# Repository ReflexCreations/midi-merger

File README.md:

# MIDI-merger

MIDI-merger is meant to be an n-to-1 merger of MIDI data. That is, you connect multiple MIDI sources with multiple cables, and all the messages sent through those are sent to a single port.

It is currently in development on the `develop` branch.

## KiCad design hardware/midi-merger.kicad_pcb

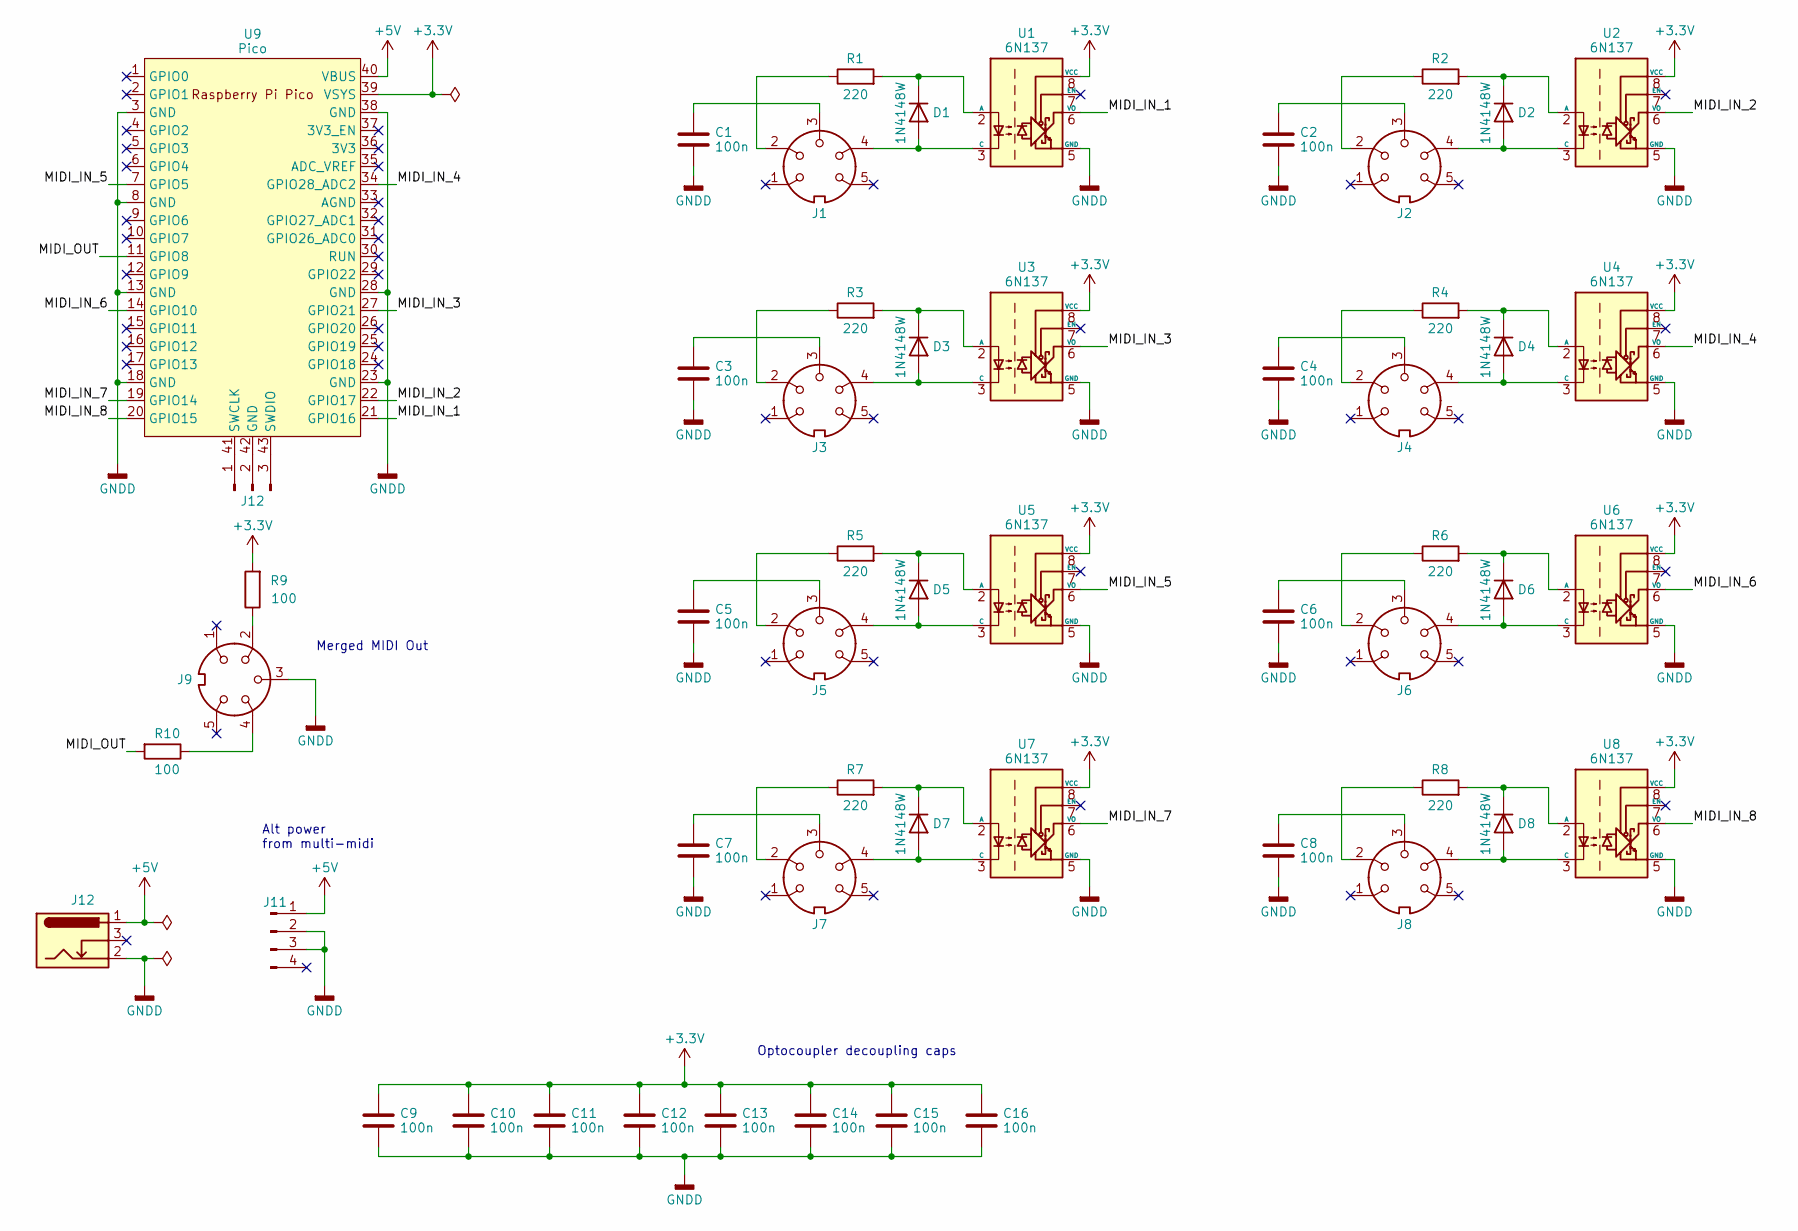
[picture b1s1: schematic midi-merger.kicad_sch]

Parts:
C1, C2, C3, C4, C5, C6, C7, C8, C9, C10, C11, C12, C13, C14, C15, C16: 100n; C_0603_1608Metric; LCSC C14663
D1, D2, D3, D4, D5, D6, D7, D8: 1N4148W; D_SOD-123; LCSC C81598
J1, J2, J3, J4, J5, J6, J7, J8, J9: DIN-5
J11: Conn_01x04_Pin; JST_EH_S4B-EH_1x04_P2.50mm_Horizontal
J12: Conn_01x03_Pin; JST_ACH_BM03B-ACHSS-GAN-ETF_1x03-1MP_P1.20mm_Vertical; LCSC C160389
R1, R2, R3, R4, R5, R6, R7, R8: 220; R_0603_1608Metric; LCSC C22962
R9, R10: 100; R_0603_1608Metric; LCSC C22775
U1, U2, U3, U4, U5, U6, U7, U8: 6N137; SSO-8_6.7x9.8mm_P2.54mm_Clearance8mm; LCSC C110020
U9: Pico; RPi_Pico_SMD_TH

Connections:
+3.3V: C9.1, C10.1, C11.1, C12.1, C13.1, C14.1, C15.1, C16.1, R9.2, U1.8 (VCC), U2.8 (VCC), U3.8 (VCC), U4.8 (VCC), U5.8 (VCC), U6.8 (VCC), U7.8 (VCC), U8.8 (VCC), U9.39 (VSYS)
/MIDI_IN_1: U1.6 (VO), U9.21 (GPIO16)
/MIDI_IN_2: U2.6 (VO), U9.22 (GPIO17)
/MIDI_IN_3: U3.6 (VO), U9.27 (GPIO21)
/MIDI_IN_4: U4.6 (VO), U9.34 (GPIO28_ADC2)
/MIDI_IN_5: U5.6 (VO), U9.7 (GPIO5)
/MIDI_IN_6: U6.6 (VO), U9.14 (GPIO10)
/MIDI_IN_7: U7.6 (VO), U9.19 (GPIO14)
/MIDI_IN_8: U8.6 (VO), U9.20 (GPIO15)
/MIDI_OUT: R10.2, U9.11 (GPIO8)
unnamed: C1.1, J1.3
unnamed: C2.1, J2.3
unnamed: C3.1, J3.3
unnamed: C4.1, J4.3
unnamed: C5.1, J5.3
unnamed: C6.1, J6.3
unnamed: C7.1, J7.3
unnamed: C8.1, J8.3
unnamed: D1.2 (A), J1.4, U1.3 (C)
unnamed: D1.1 (K), R1.2, U1.2 (A)
unnamed: D2.2 (A), J2.4, U2.3 (C)
unnamed: D2.1 (K), R2.2, U2.2 (A)
unnamed: D3.2 (A), J3.4, U3.3 (C)
unnamed: D3.1 (K), R3.2, U3.2 (A)
unnamed: D4.2 (A), J4.4, U4.3 (C)
unnamed: D4.1 (K), R4.2, U4.2 (A)
unnamed: D5.2 (A), J5.4, U5.3 (C)
unnamed: D5.1 (K), R5.2, U5.2 (A)
unnamed: D6.2 (A), J6.4, U6.3 (C)
unnamed: D6.1 (K), R6.2, U6.2 (A)
unnamed: D7.2 (A), J7.4, U7.3 (C)
unnamed: D7.1 (K), R7.2, U7.2 (A)
unnamed: D8.2 (A), J8.4, U8.3 (C)
unnamed: D8.1 (K), R8.2, U8.2 (A)
unnamed: J1.2, R1.1
unnamed: J2.2, R2.1
unnamed: J3.2, R3.1
unnamed: J4.2, R4.1
unnamed: J5.2, R5.1
unnamed: J6.2, R6.1
unnamed: J7.2, R7.1
unnamed: J8.2, R8.1
unnamed: J9.2, R9.1
unnamed: J9.4, R10.1
unnamed: J12.3, U9.43 (SWDIO)

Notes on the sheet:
Merged MIDI Out
Optocoupler decoupling caps
Alt power from multi-midi

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
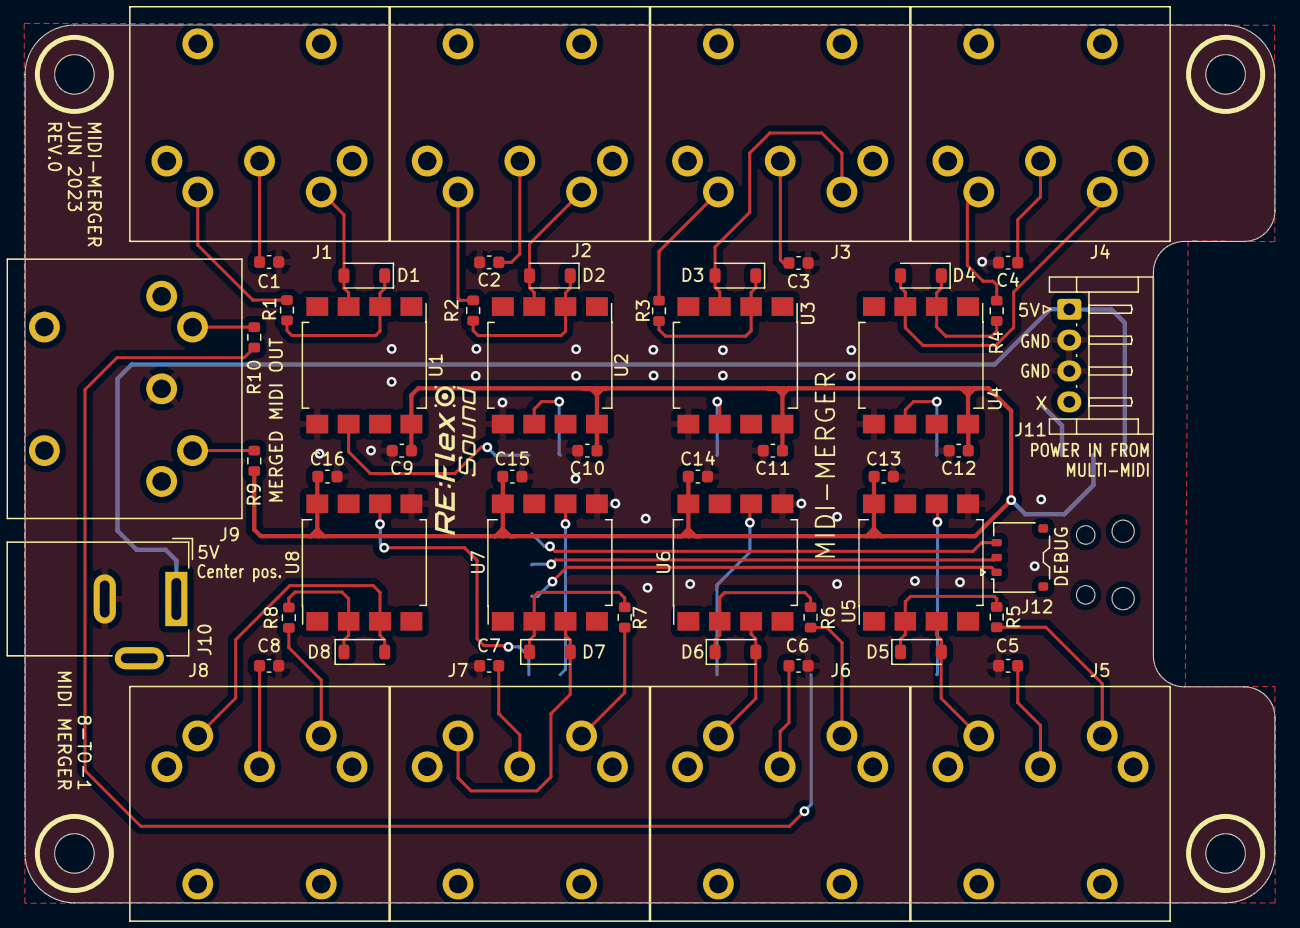
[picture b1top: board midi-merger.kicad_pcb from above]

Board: 2 copper layers, 101.2 x 71.1 mm, 55 parts (1 on the bottom side), 49 nets.

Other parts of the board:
J10: Barrel_Jack_Switch; BarrelJack_Wuerth_6941xx301002

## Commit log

2023-05-26 Initial commit: placeholder README
2023-05-26 Add firmware for 3->1 prototype w/ SoftwareSerial
    Hoping to use Programmable IO feature of the RP2040 for UART RX instead.
2023-05-28 Rewrite firmware with PIO UARTs
    These should perform a lot better than SoftwareSerial.
    I didn't want to even try getting PIO-based UARTs working with the MIDI
    library, so I implemented the minimum MIDI logic required for correctly
    merging MIDI messages into one output. Essentially ensuring messages
    remain intact, sysex dumps can only be interleaved with system realtime
    messages, stuff like that.
2023-06-02 Add PCB design for a 8-to-1 midi-merger
2023-06-02 Firmware: map inputs to pins in hardware design
